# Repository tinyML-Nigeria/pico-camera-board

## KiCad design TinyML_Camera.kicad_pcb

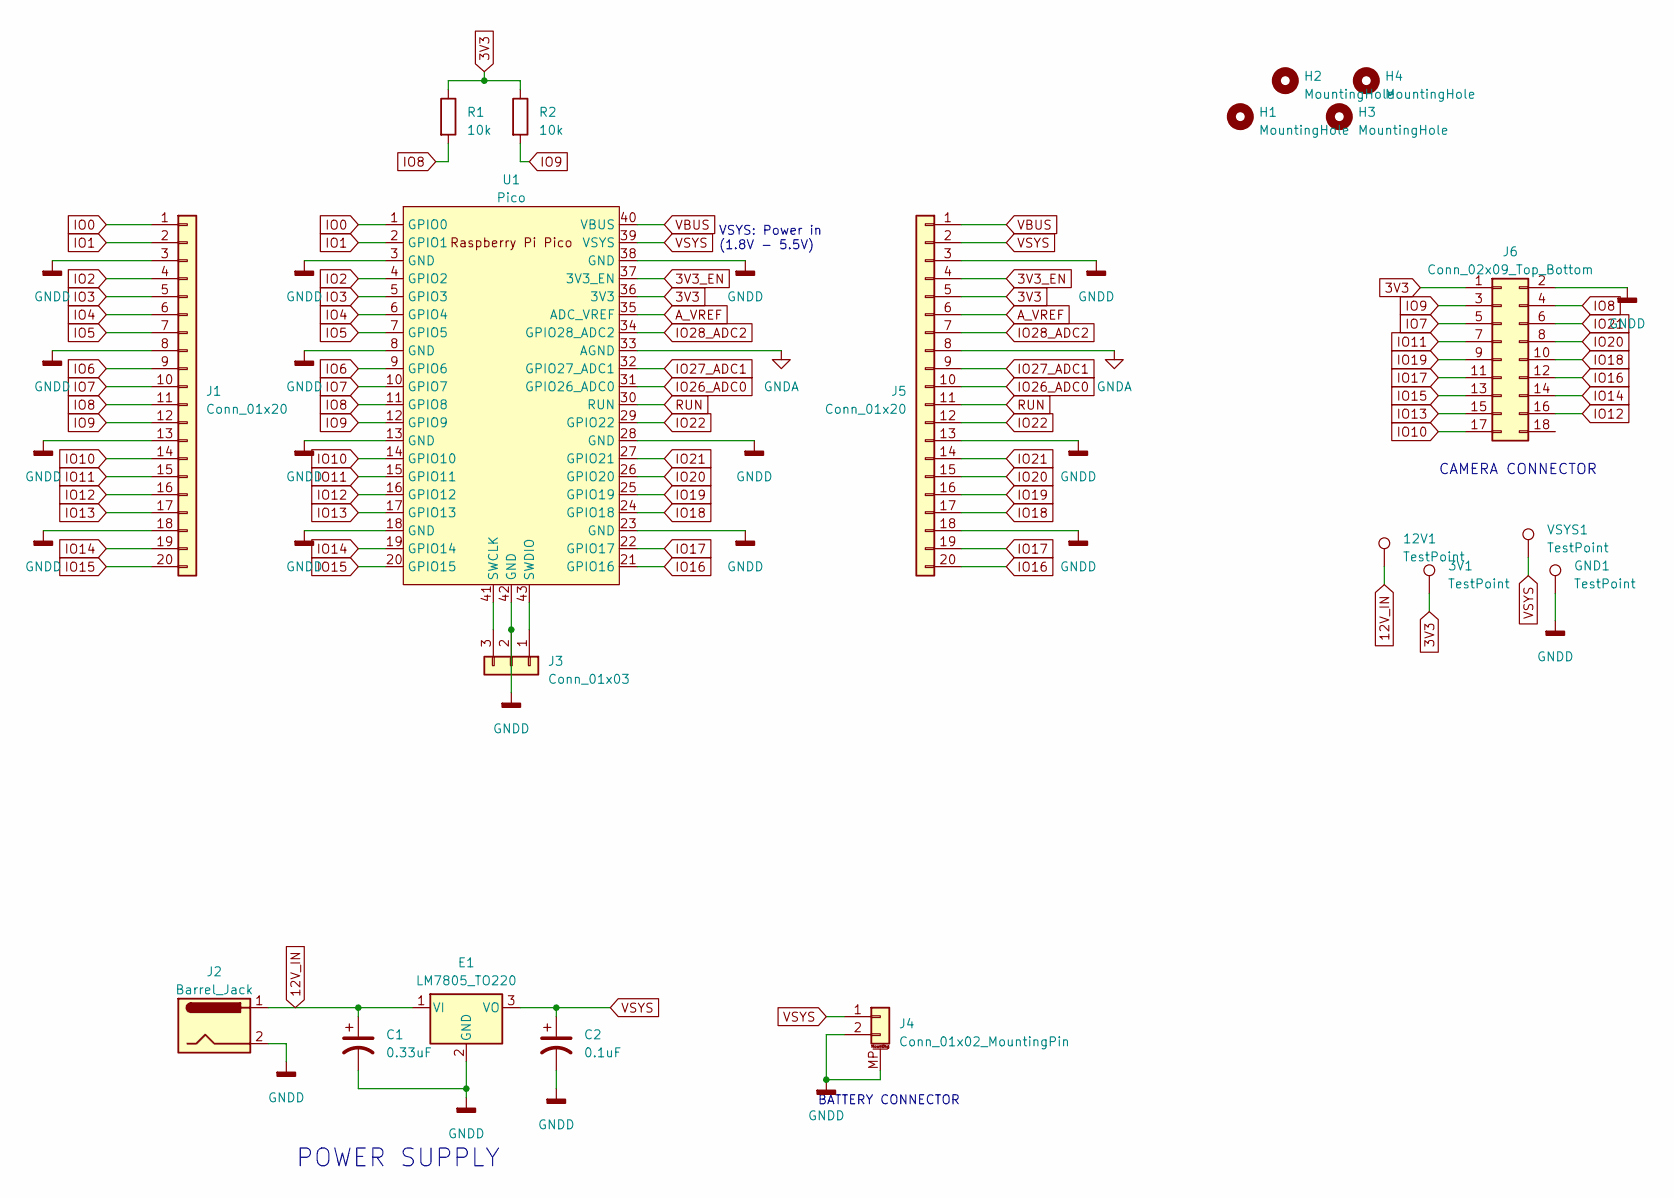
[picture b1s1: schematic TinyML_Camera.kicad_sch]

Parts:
3V1, 12V1: TestPoint; TestPoint_Pad_D1.5mm
C1: 0.33uF; CP_Radial_D5.0mm_P2.50mm
C2: 0.1uF; CP_Radial_D5.0mm_P2.50mm
E1: LM7805_TO220; TO-220-3_Horizontal_TabDown
GND1: TestPoint; TestPoint_Pad_D1.5mm
H1, H2, H3, H4: MountingHole; MountingHole_2.7mm_Pad
J1, J5: Conn_01x20; PinSocket_1x20_P2.54mm_Vertical
J2: Barrel_Jack; BarrelJack_GCT_DCJ200-10-A_Horizontal
J3: Conn_01x03; PinSocket_1x03_P2.54mm_Vertical
J4: Conn_01x02_MountingPin; JST_EH_B2B-EH-A_1x02_P2.50mm_Vertical
J6: Conn_02x09_Top_Bottom; PinSocket_2x09_P2.54mm_Vertical
R1, R2: 10k; R_Axial_DIN0207_L6.3mm_D2.5mm_P10.16mm_Horizontal
U1: Pico; RPi_Pico_SMD_TH
VSYS1: TestPoint; TestPoint_Pad_D1.5mm

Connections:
3V3: 3V1.1, J5.5, J6.1, R1.1, R2.1, U1.36 (3V3)
3V3_EN: J5.4, U1.37 (3V3_EN)
12V_IN: 12V1.1, C1.1, E1.1 (VI), J2.1
A_VREF: J5.6, U1.35 (ADC_VREF)
GNDA: J5.8, U1.33 (AGND)
GNDD: C1.2, C2.2, E1.2 (GND), GND1.1, J1.3, J1.8, J1.13, J1.18, J2.2, J3.2, J4.2, J4.MP (MountPin), J5.3, J5.13, J5.18, J6.2, U1.3 (GND), U1.8 (GND), U1.13 (GND), U1.18 (GND), U1.23 (GND), U1.28 (GND), U1.38 (GND), U1.42 (GND)
IO0: J1.1, U1.1 (GPIO0)
IO1: J1.2, U1.2 (GPIO1)
IO2: J1.4, U1.4 (GPIO2)
IO3: J1.5, U1.5 (GPIO3)
IO4: J1.6, U1.6 (GPIO4)
IO5: J1.7, U1.7 (GPIO5)
IO6: J1.9, U1.9 (GPIO6)
IO7: J1.10, J6.5, U1.10 (GPIO7)
IO8: J1.11, J6.4, R1.2, U1.11 (GPIO8)
IO9: J1.12, J6.3, R2.2, U1.12 (GPIO9)
IO10: J1.14, J6.17, U1.14 (GPIO10)
IO11: J1.15, J6.7, U1.15 (GPIO11)
IO12: J1.16, J6.16, U1.16 (GPIO12)
IO13: J1.17, J6.15, U1.17 (GPIO13)
IO14: J1.19, J6.14, U1.19 (GPIO14)
IO15: J1.20, J6.13, U1.20 (GPIO15)
IO16: J5.20, J6.12, U1.21 (GPIO16)
IO17: J5.19, J6.11, U1.22 (GPIO17)
IO18: J5.17, J6.10, U1.24 (GPIO18)
IO19: J5.16, J6.9, U1.25 (GPIO19)
IO20: J5.15, J6.8, U1.26 (GPIO20)
IO21: J5.14, J6.6, U1.27 (GPIO21)
IO22: J5.12, U1.29 (GPIO22)
IO26_ADC0: J5.10, U1.31 (GPIO26_ADC0)
IO27_ADC1: J5.9, U1.32 (GPIO27_ADC1)
IO28_ADC2: J5.7, U1.34 (GPIO28_ADC2)
unnamed: J3.1, U1.43 (SWDIO)
unnamed: J3.3, U1.41 (SWCLK)
RUN: J5.11, U1.30 (RUN)
VBUS: J5.1, U1.40 (VBUS)
VSYS: C2.1, E1.3 (VO), J4.1, J5.2, U1.39 (VSYS), VSYS1.1

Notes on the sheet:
BATTERY CONNECTOR
POWER SUPPLY
VSYS: Power in (1.8V - 5.5V)
CAMERA CONNECTOR

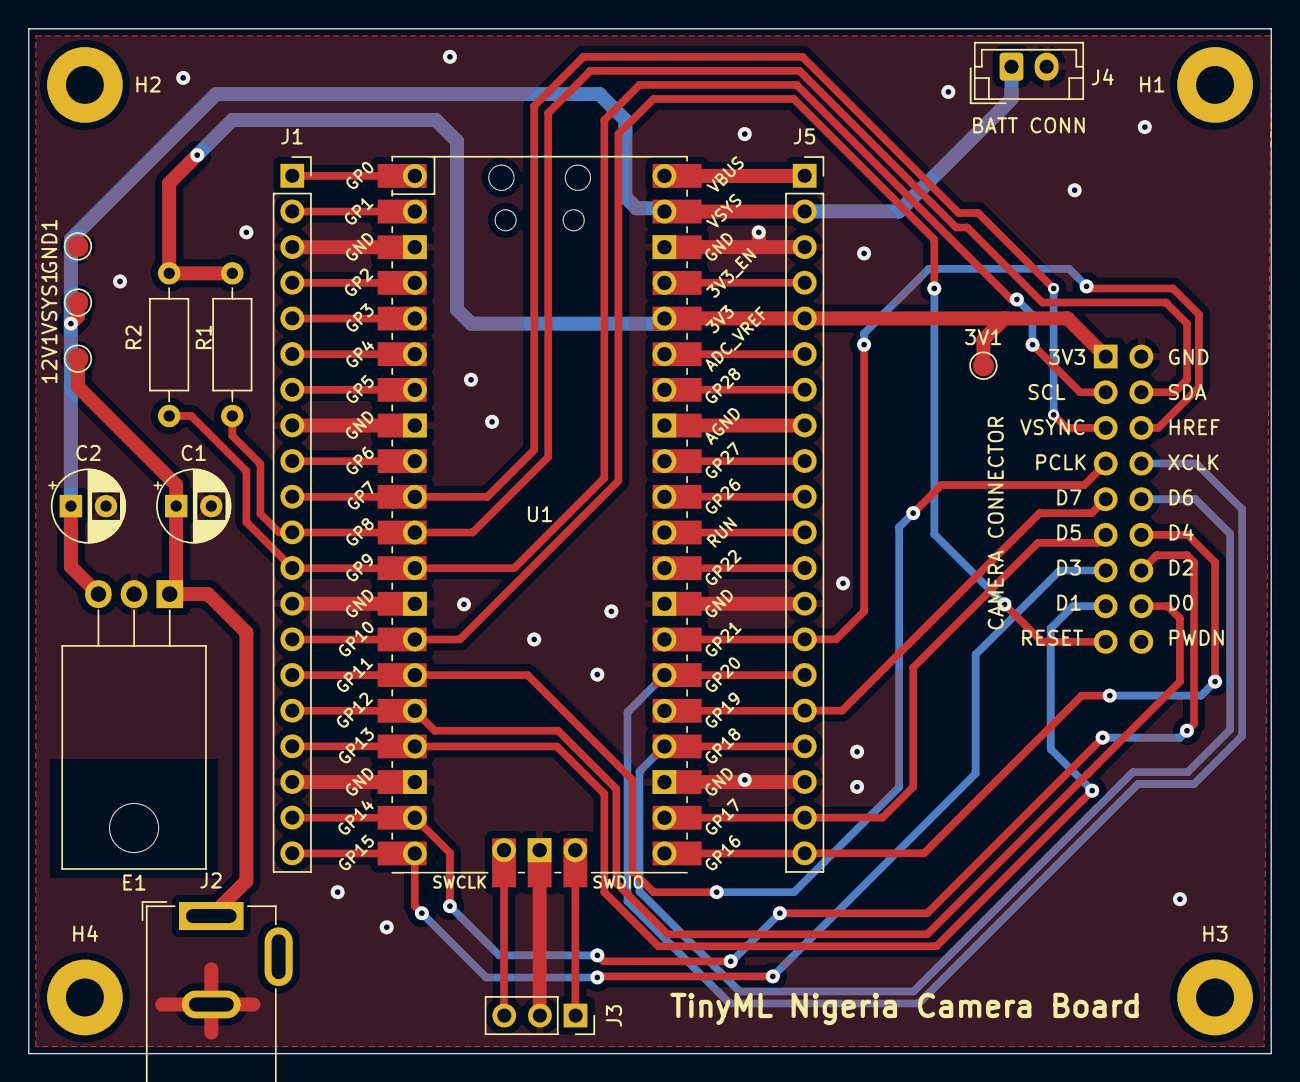
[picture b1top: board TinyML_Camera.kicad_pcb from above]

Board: 2 copper layers, 88.5 x 73.0 mm, 20 parts (1 on the bottom side), 37 nets.

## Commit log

2023-09-03 camera board files
